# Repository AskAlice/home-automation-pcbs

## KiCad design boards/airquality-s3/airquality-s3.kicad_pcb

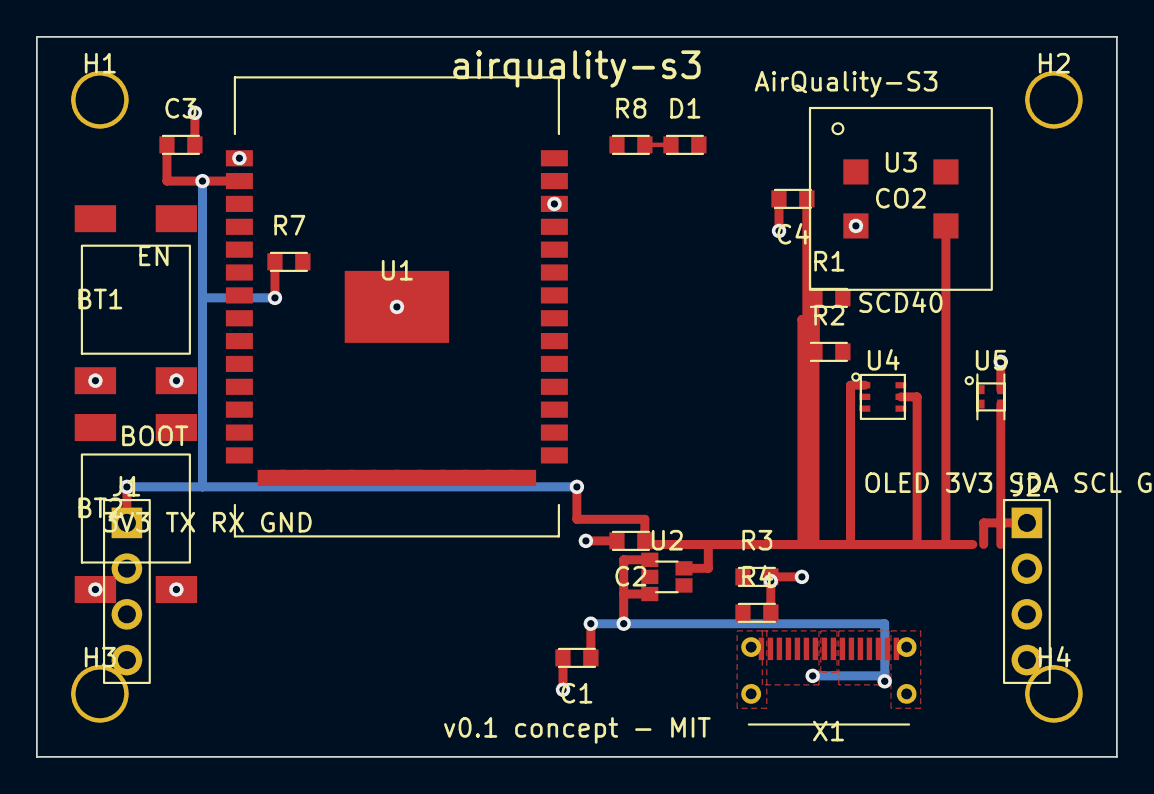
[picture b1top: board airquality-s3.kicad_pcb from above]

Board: 2 copper layers, 60.0 x 40.0 mm, 25 parts (0 on the bottom side), 15 nets.

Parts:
BT1, BT2: SW_PUSH; Tactile-6x6-SMD
C1, C2: 10uF; C_0603_1608Metric
C3, C4: 100nF; C_0603_1608Metric
D1: LED_GRN; LED_0603_1608Metric
H1, H2, H3, H4: MountingHole_M2.5
J1, J2: Conn_01x04; PinHeader_1x04_P2.54mm_Vertical
R1, R2: 4.7k; R_0603_1608Metric
R3, R4: 5.1k; R_0603_1608Metric
R7: 10k; R_0603_1608Metric
R8: 1k; R_0603_1608Metric
U1: ESP32-S3-WROOM-1
U2: AP2112K-3.3; SOT-23-5
U3: SCD40
U4: SGP40; SGP40-DFN6
U5: SHT40; SHT40-DFN4
X1: USB_C_16P; USB_C_Receptacle_USB2.0_16P

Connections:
+3V3: C2.1, C3.1, C4.1, J1.1, J2.1, R1.1, R2.1, R7.1, R8.1, U1.2, U2.5, U3.3, U4.1, U4.5, U5.3
BOOT: BT1.1, BT1.3, BT2.1, BT2.3, U1.25
EN: R7.2, U1.3
GND: BT1.2, BT1.4, BT2.2, BT2.4, C1.2, C2.2, C3.2, C4.2, J1.4, J2.4, R3.2, R4.2, U1.1, U1.38, U1.41, U2.2, U3.2, U4.2, U4.4, U5.4, X1.1, X1.8, X1.9, X1.16, X1.S1, X1.S2, X1.S3, X1.S4
I2C_SCL: J2.3, R2.2, U1.15, U3.1, U4.6, U5.2
I2C_SDA: J2.2, R1.2, U1.12, U3.4, U4.3, U5.1
LED1_A: D1.1, R8.2
RX0: J1.3, U1.34
STAT_LED: D1.2, U1.29
TX0: J1.2, U1.35
USB_CC1: R3.1, X1.3
USB_CC2: R4.1, X1.14
USB_DM: U1.39, X1.5, X1.12
USB_DP: U1.40, X1.4, X1.13
VBUS: C1.1, U2.1, U2.3, X1.2, X1.7, X1.10, X1.15

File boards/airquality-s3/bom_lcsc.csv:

ref,value,footprint,lcsc,mpn,qty
U1,ESP32-S3-WROOM-1,airquality-s3:ESP32-S3-WROOM-1,C2913198,ESP32-S3-WROOM-1-N8,1
X1,USB_C_16P,Connector_USB:USB_C_Receptacle_USB2.0_16P,C165948,TYPE-C-31-M-12,1
U2,AP2112K-3.3,Package_TO_SOT_SMD:SOT-23-5,C51115,AP2112K-3.3TRG1,1
U3,SCD40,airquality-s3:SCD40,C3659421,SCD40-D-R2,1
U4,SGP40,airquality-s3:SGP40-DFN6,C2874215,SGP40-D-R4,1
U5,SHT40,airquality-s3:SHT40-DFN4,C2909890,SHT40-AD1B-R2,1
BT1,BT2,SW_PUSH,airquality-s3:Tactile-6x6-SMD,C139797,TS-1187A-B-A-B,2
D1,LED_GRN,LED_SMD:LED_0603_1608Metric,C2297,LTST-C190KGKT,1
R1,R2,4.7k,Resistor_SMD:R_0603_1608Metric,C23162,0603WAF4701T5E,2
R3,R4,5.1k,Resistor_SMD:R_0603_1608Metric,C23186,0603WAF5101T5E,2
R7,10k,Resistor_SMD:R_0603_1608Metric,C25804,0603WAF1002T5E,1
R8,1k,Resistor_SMD:R_0603_1608Metric,C21190,0603WAF1001T5E,1
C1,C2,10uF,Capacitor_SMD:C_0603_1608Metric,C15849,CL10A106KP8NNNC,2
C3,C4,100nF,Capacitor_SMD:C_0603_1608Metric,C14663,0603B104K500NT,2
J1,J2,Conn_01x04,Connector_PinHeader_2.54mm:PinHeader_1x04_P2.54mm_Vertical,C49258,KH-2.54PH180-1X4P-L13.5,2

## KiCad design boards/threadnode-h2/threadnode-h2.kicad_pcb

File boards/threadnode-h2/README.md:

# threadnode-h2 — battery Thread contact/button node (SPEC 7.1)

ESP32-H2-MINI-1 node on CR2032 with reed-switch input, user button, I2C
expansion header, and programming header. **v0.1 concept board.**

- Board: 40 × 30 mm, 2-layer, 3 mounting holes
- Power: CR2032 (BT1) direct to +3V3 (no LDO) — brown-out risk below ~2.6 V
- Status: `python3 boards/wave2/wave2gen.py threadnode-h2` → self-check OK

## BOM (bom_lcsc.csv)

| Ref | Value | Footprint | LCSC # | MPN | Qty |
|---|---|---|---|---|---|
| U1 | ESP32-H2-MINI-1 | ESP32-H2-MINI-1 | C2924539 | ESP32-H2-MINI-1-N4 | 1 |
| BT1 | CR2032 | custom:CR2032-SMD | C70377 | MY-BS-03-A1AJ | 1 |
| SW1 | Reed switch | custom:Reed-MK24 | C140342 | MK24-B-2 | 1 |
| D1 | LED green | 0603 | C72043 | 19-217/GHC-YR1S2/3T | 1 |
| R8 | 1k | 0603 | C21190 | 0603WAF1001T5E | 1 |
| R4,R5 | 4.7k | 0603 | C23162 | 0603WAF4701T5E | 2 |
| R1,R2,R3,R7 | 10k | 0603 | C98252 | 0603WAF1002T5E | 4 |
| C1,C2,C3 | 100nF | 0603 | C14663 | CL10B104KB8NNNC | 3 |
| BT2 | SW_PUSH | custom:Tactile-6x6-SMD | C91808 | TS-1187A-B-A-B | 1 |
| J1 | Conn_01x04 (3V3/TX0/RX0/GND) | PinHeader_1x04_P2.54mm | C49241 | A2541WV-4P | 1 |
| J2 | Conn_01x04 (3V3/SDA/SCL/GND) | PinHeader_1x04_P2.54mm | C49241 | A2541WV-4P | 1 |

## Pinout (H2-MINI-1)

| Signal | GPIO | Notes |
|---|---|---|
| REED | GPIO3 | reed switch to GND, deep-sleep wakeup |
| I2C_SDA / I2C_SCL | GPIO12 / GPIO13 | J2 header, 4.7k pull-ups R4/R5 |
| STAT_LED | GPIO8 | green LED via R8 (pulse only — battery) |
| BTN (BOOT) | GPIO9 | user button; hold at reset = ROM bootloader |
| TX0 / RX0 | GPIO24 / GPIO23 | J1 prog header (flash + log; **no USB**) |
| EN | — | R1 10k pull-up + C3 100nF |

## Firmware

See `esphome/threadnode-h2.yaml`. H2 has **no Wi-Fi** — production firmware
targets Matter-over-Thread (esp-matter) or Zigbee; yaml validates the I/O
map with logger + deep-sleep on GPIO3.

## Routing status

**v0.1 concept — signals left for autorouting.** Power rails (+3V3/GND/EN)
routed with B.Cu trunk + F.Cu drops and GND via-stitching; all signal nets
(I2C, UART, reed, LED) are unrouted ratsnest.

## Analyzer notes

`analyze_pcb.py`: **DFM-001 = 0**. Expect RT-001 unrouted-net errors (by
design, signals left for autorouting) and PM courtyard notes around the
CR2032 holder / tactile button GND pads touching GND mounting-hole copper
(electrically joined by design).

## Caveats (verify before fabrication!)

- CR2032 voltage (2.8–3.6 V) grazes the H2 brown-out threshold; short LED
  pulses only. Verify with esp-idf brownout settings.
- I2C pads (J2) are on strapping-adjacent GPIOs — double-check the H2
  datasheet (GPIO8/9/25/26/27 strapping) before reusing.
- No USB connector: flash via J1 (3V3/TX0/RX0/GND) or add USB-JTAG wiring.
- **Verify all footprints, pin numbers, and clearances against KiCad
  libraries + datasheets before ordering boards.**

## Renders

| Raytraced 3D (KiCad) | 2D layout |
|---|---|
|  |  |
|  |  |

🎬 24 real KiCad raytraced frames stitched with ffmpeg (tools/turntable.sh).

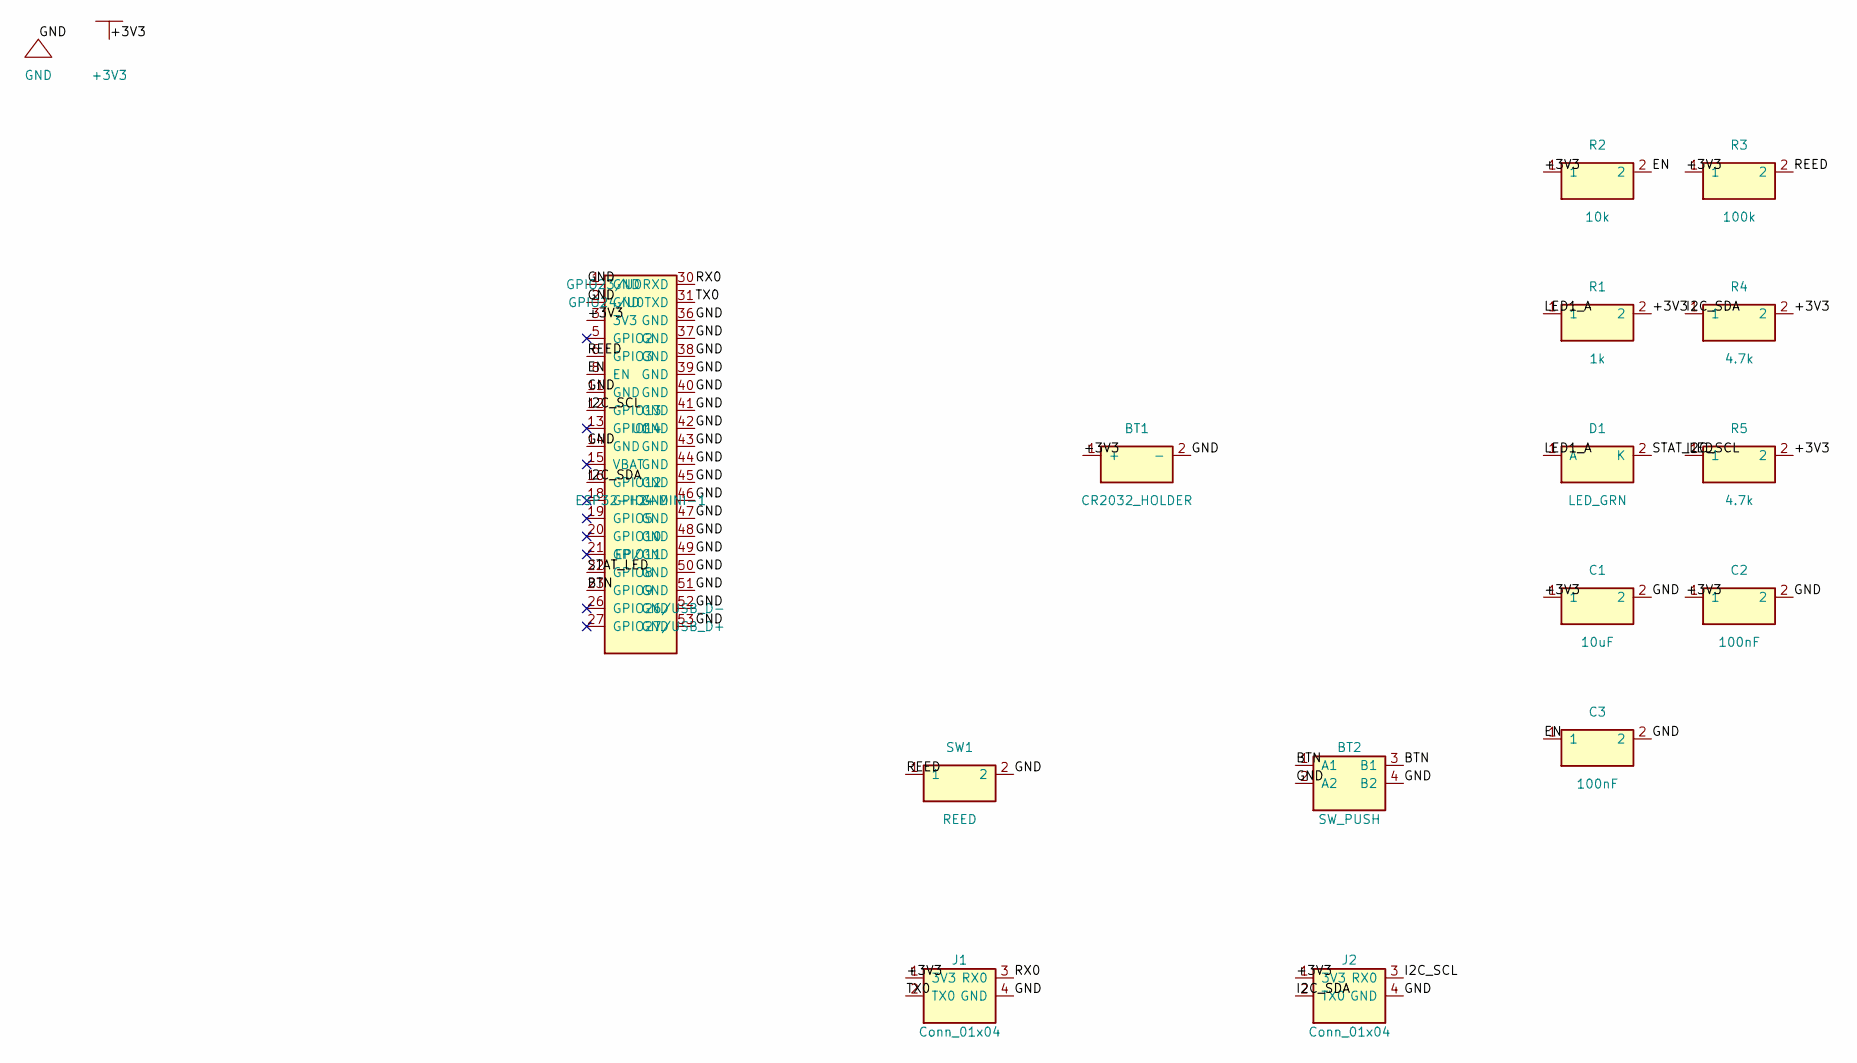
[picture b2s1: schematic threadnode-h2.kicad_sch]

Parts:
BT1: CR2032_HOLDER; CR2032-holder; LCSC C5239862
BT2: SW_PUSH; Tactile-6x6-SMD; LCSC C139797
C1: 10uF; C_0603_1608Metric; LCSC C15849
C2, C3: 100nF; C_0603_1608Metric; LCSC C14663
D1: LED_GRN; LED_0603_1608Metric; LCSC C2297
J1, J2: Conn_01x04; PinHeader_1x04_P2.54mm_Vertical; LCSC C49258
R1: 1k; R_0603_1608Metric; LCSC C21190
R2: 10k; R_0603_1608Metric; LCSC C25804
R3: 100k; R_0603_1608Metric; LCSC C25803
R4, R5: 4.7k; R_0603_1608Metric; LCSC C23162
SW1: REED; Reed-SMD; LCSC C315909
U1: ESP32-H2-MINI-1; LCSC —

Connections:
+3V3: BT1.1 (+), C1.1, C2.1, J1.1 (3V3), J2.1 (3V3), R1.2, R2.1, R3.1, R4.2, R5.2, U1.3 (3V3)
BTN: BT2.1 (A1), BT2.3 (B1), U1.23 (GPIO9)
EN: C3.1, R2.2, U1.8 (EN)
GND: BT1.2 (-), BT2.2 (A2), BT2.4 (B2), C1.2, C2.2, C3.2, J1.4 (GND), J2.4 (GND), SW1.2, U1.1 (GND), U1.2 (GND), U1.11 (GND), U1.14 (GND), U1.36 (GND), U1.37 (GND), U1.38 (GND), U1.39 (GND), U1.40 (GND), U1.41 (GND), U1.42 (GND), U1.43 (GND), U1.44 (GND), U1.45 (GND), U1.46 (GND), U1.47 (GND), U1.48 (GND), U1.49 (EP/GND), U1.50 (GND), U1.51 (GND), U1.52 (GND), U1.53 (GND)
I2C_SCL: J2.3 (RX0), R5.1, U1.12 (GPIO13)
I2C_SDA: J2.2 (TX0), R4.1, U1.16 (GPIO12)
LED1_A: D1.1 (A), R1.1
REED: R3.2, SW1.1, U1.6 (GPIO3)
RX0: J1.3 (RX0), U1.30 (GPIO23/U0RXD)
STAT_LED: D1.2 (K), U1.22 (GPIO8)
TX0: J1.2 (TX0), U1.31 (GPIO24/U0TXD)

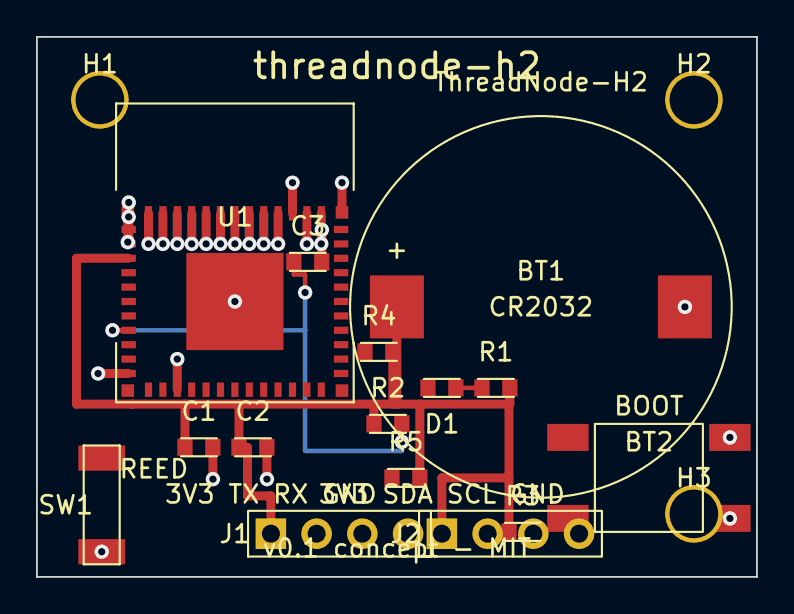
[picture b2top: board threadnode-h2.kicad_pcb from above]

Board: 2 copper layers, 40.0 x 30.0 mm, 18 parts (0 on the bottom side), 11 nets.

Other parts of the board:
H1, H2, H3: MountingHole_M2.5

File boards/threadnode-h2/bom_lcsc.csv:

ref,value,footprint,lcsc,mpn,qty
U1,ESP32-H2-MINI-1,threadnode-h2:ESP32-H2-MINI-1,—,ESP32-H2-MINI-1-N4,1
BT1,CR2032_HOLDER,threadnode-h2:CR2032-holder,C5239862,BS-02-A1AJ010,1
SW1,REED,threadnode-h2:Reed-SMD,C315909,59170-1-S-00-D,1
BT2,SW_PUSH,threadnode-h2:Tactile-6x6-SMD,C139797,TS-1187A-B-A-B,1
D1,LED_GRN,LED_SMD:LED_0603_1608Metric,C2297,LTST-C190KGKT,1
R1,1k,Resistor_SMD:R_0603_1608Metric,C21190,0603WAF1001T5E,1
R2,10k,Resistor_SMD:R_0603_1608Metric,C25804,0603WAF1002T5E,1
R3,100k,Resistor_SMD:R_0603_1608Metric,C25803,0603WAF1003T5E,1
R4,R5,4.7k,Resistor_SMD:R_0603_1608Metric,C23162,0603WAF4701T5E,2
C1,10uF,Capacitor_SMD:C_0603_1608Metric,C15849,CL10A106KP8NNNC,1
C2,C3,100nF,Capacitor_SMD:C_0603_1608Metric,C14663,0603B104K500NT,2
J1,J2,Conn_01x04,Connector_PinHeader_2.54mm:PinHeader_1x04_P2.54mm_Vertical,C49258,KH-2.54PH180-1X4P-L13.5,2
